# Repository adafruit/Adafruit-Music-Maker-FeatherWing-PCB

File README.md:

## Adafruit Music Maker FeatherWing PCB

<a href="http://www.adafruit.com/products/3357">&nbsp; 
<a href="http://www.adafruit.com/products/3436"><br/>
Click a picture to purchase from the Adafruit shop</a>

PCB files for the Adafruit Music Maker FeatherWings. Format is EagleCAD schematic and board layout

For more details, check out the product pages at
  * Music Maker FeatherWing http://www.adafruit.com/products/3357
  * Music Maker FeatherWing with 3W amp http://www.adafruit.com/products/3436

### Description

Bend all audio files to your will with the Adafruit Music Maker FeatherWings! It's a fun-size version of our Music Maker shield for Arduino! This powerful wing features the VS1053, an encoding/decoding (codec) chip that can decode a wide variety of audio formats such as MP3, AAC, Ogg Vorbis, WMA, MIDI, FLAC, WAV (PCM and ADPCM). You can do all sorts of stuff with the audio as well such as adjusting bass, treble, and volume digitally.

All this functionality is implemented in a light-weight SPI interface so that any Feather Board can play audio from an SD card. There's also a special MIDI mode that you can boot the chip into that will read 'classic' 31250Kbaud MIDI data from the UART TX pin and act like a synth/drum machine - there are dozens of built-in drum and sample effects!

What a great musical add-on to your Feather! That's why we spun up this super FeatherWing, perfect for use with any of our Feather Boards! Music playback testing working with ATmega32u4, ATSAMD M0, ESP8266, WICED Teensy 3, and nRF52 Feathers. MIDI playback works with all Feathers but you may need to remove the 'Wing during programming and also for USB-Serial Feathers like the ESP8266 and nRF52 you'll end up re-using the main Serial console for MIDI which can be confusing.

### License

Adafruit invests time and resources providing this open source design, please support Adafruit and open-source hardware by purchasing products from [Adafruit](https://www.adafruit.com)!

Designed by Limor Fried/Ladyada for Adafruit Industries.

Creative Commons Attribution/Share-Alike, all text above must be included in any redistribution. See license.txt for additional details.

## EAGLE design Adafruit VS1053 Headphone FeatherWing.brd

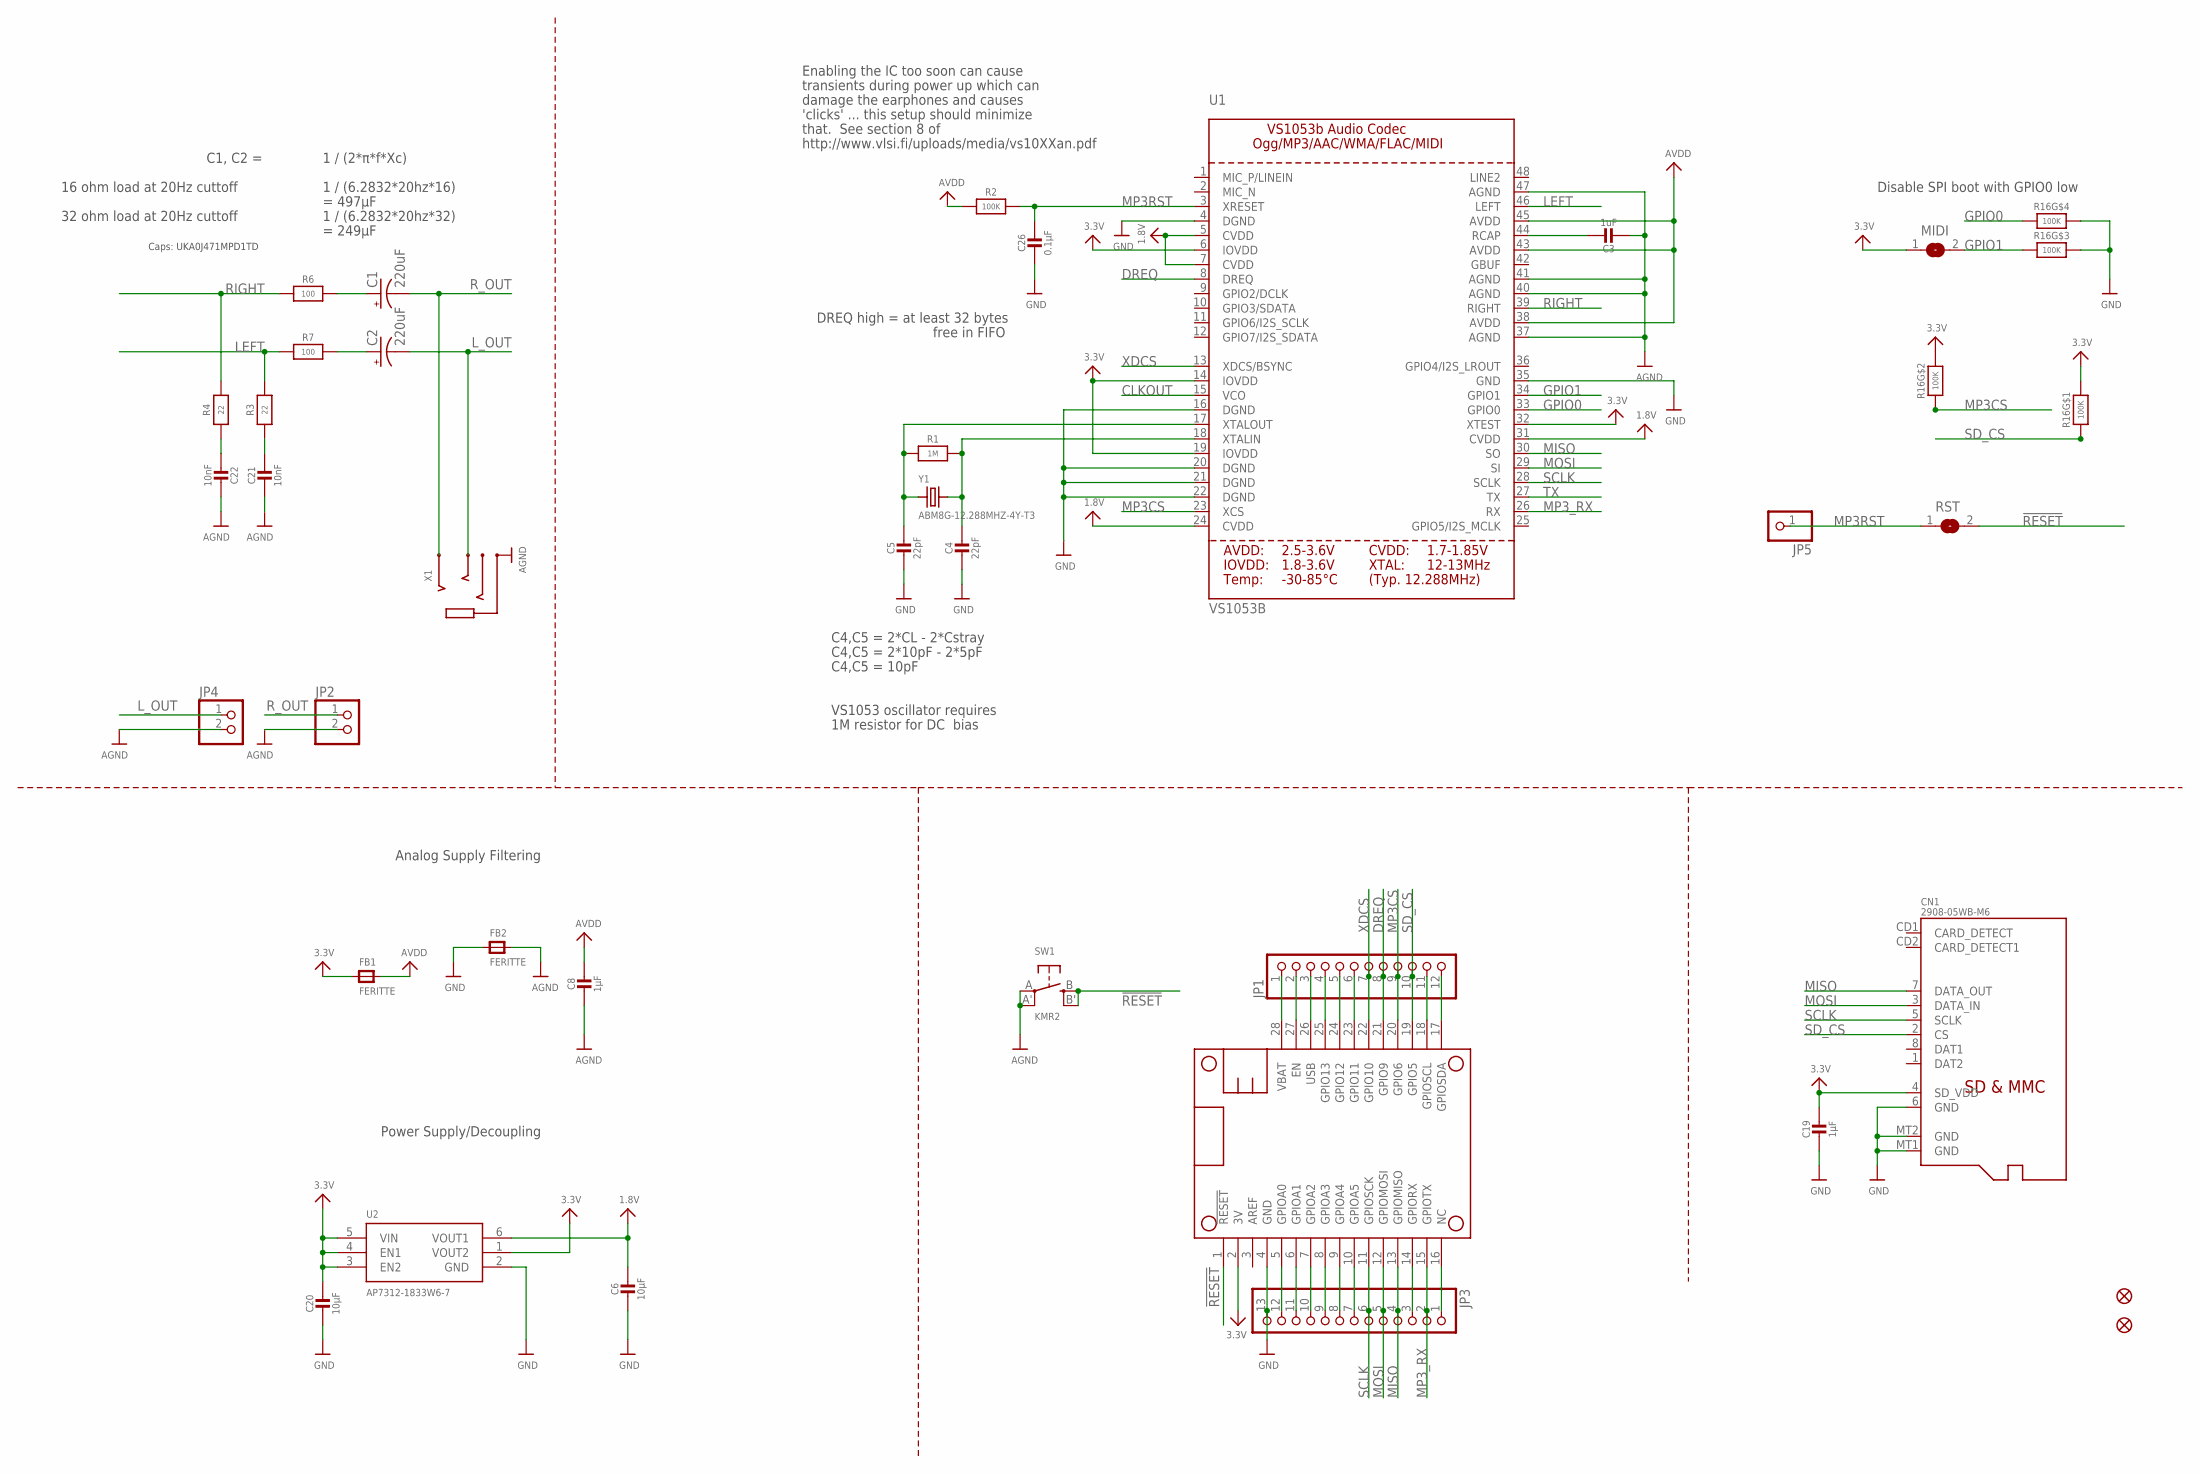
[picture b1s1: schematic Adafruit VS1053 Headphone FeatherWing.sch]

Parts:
C1, C2: 220uF; PANASONIC_C
C3: 1uF; 0603-NO
C4, C5: 22pF; 0603-NO
C6: 10µF; _0805MP
C8, C19: 1µF; 0603-NO
C20: 10µF; 0805-NO
C21, C22: 10nF; 0603-NO
C26: 0.1µF; 0603-NO
CN1: 2908-05WB-M6; MICROSD
FB1, FB2: FERITTE; 0805-NO
FID1, FID2: FIDUCIAL""; FIDUCIAL_1MM
JP1: HEADER-1X12; 1X12_ROUND
JP2, JP4: HEADER-1X2ROUND; 1X02_ROUND
JP3: HEADER-1X13; 1X13_ROUND_70
JP5: HEADER-1X1ROUND; 1X01_ROUND
MIDI: SOLDERJUMPER; SOLDERJUMPER_ARROW_NOPASTE
MS1: FEATHERWING_NODIM
R1: 1M; 0603-NO
R2: 100K; 0603-NO
R3, R4: 22; 0603-NO
R6, R7: 100; 0603-NO
R16: 100K; RESPACK_4X0603
RST: SOLDERJUMPERCLOSED; SOLDERJUMPER_CLOSEDWIRE
SW1: KMR2; BTN_KMR2_4.6X2.8
U1: VS1053B; LQFP48
U2: AP7312-1833W6-7; SOT23-6
X1: AUDIO_3.5MMJACK_4POL; 4UCONN_18510
Y1: ABM8G-12.288MHZ-4Y-T3; CRYSTAL_3.2X2.5

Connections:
1.8V: C6.1, U1.5 (CVDD), U1.7 (CVDD), U1.24 (CVDD), U1.31 (CVDD), U2.6 (VOUT1)
3.3V: C19.1, C20.1, CN1.4 (SD_VDD), FB1.1, MIDI.1, MS1.2 (3V), R16.7 (2), R16.8 (2), U1.6 (IOVDD), U1.14 (IOVDD), U1.19 (IOVDD), U1.32 (XTEST), U2.1 (VOUT2), U2.3 (EN2), U2.4 (EN1), U2.5 (VIN)
!RESET: MS1.1 (!RESET), RST.2, SW1.B (S), SW1.B' (S1)
AGND: C3.2, C8.2, C21.2, C22.2, FB2.2, JP2.2, JP4.2, SW1.A, SW1.A' (P1), U1.37 (AGND), U1.40 (AGND), U1.41 (AGND), U1.47 (AGND), X1.1-GND (TIP)
AVDD: C8.1, FB1.2, R2.1, U1.38 (AVDD), U1.43 (AVDD), U1.45 (AVDD)
CLKOUT: U1.15 (VCO)
DREQ: JP1.8, MS1.21 (GPIO9), U1.8 (DREQ)
GND: C4.2, C5.2, C6.2, C19.2, C20.2, C26.2, CN1.6 (GND), CN1.MT1 (GND), CN1.MT2 (GND), FB2.1, JP3.13, MS1.4 (GND), R16.5 (2), R16.6 (2), U1.4 (DGND), U1.16 (DGND), U1.20 (DGND), U1.21 (DGND), U1.22 (DGND), U1.35 (GND), U2.2 (GND)
GPIO0: R16.4 (1), U1.33 (GPIO0)
GPIO1: MIDI.2, R16.3 (1), U1.34 (GPIO1)
LEFT: R3.1, R7.2, U1.46 (LEFT)
LEFT_FILTERED: C2.+, R7.1
L_OUT: C2.-, JP4.1, X1.2-TIP (RING3)
MISO: CN1.7 (DATA_OUT), JP3.4, MS1.13 (GPIOMISO), U1.30 (SO)
MOSI: CN1.3 (DATA_IN), JP3.5, MS1.12 (GPIOMOSI), U1.29 (SI)
MP3CS: JP1.9, MS1.20 (GPIO6), R16.2 (1), U1.23 (XCS)
MP3RST: C26.1, JP5.1, R2.2, RST.1, U1.3 (XRESET)
MP3_RX: JP3.2, MS1.15 (GPIOTX), U1.26 (RX)
unnamed: C5.1, R1.1, U1.17 (XTALOUT), Y1.1
unnamed: C4.1, R1.2, U1.18 (XTALIN), Y1.2
unnamed: C3.1, U1.44 (RCAP)
unnamed: JP1.2, MS1.27 (EN)
unnamed: C21.1, R3.2
unnamed: C22.1, R4.2
unnamed: JP1.4, MS1.25 (GPIO13)
unnamed: JP1.5, MS1.24 (GPIO12)
unnamed: JP1.6, MS1.23 (GPIO11)
unnamed: JP1.11, MS1.18 (GPIOSCL)
unnamed: JP1.12, MS1.17 (GPIOSDA)
unnamed: JP3.1, MS1.16 (NC)
unnamed: JP3.3, MS1.14 (GPIORX)
unnamed: JP3.7, MS1.10 (GPIOA5)
unnamed: JP3.8, MS1.9 (GPIOA4)
unnamed: JP3.9, MS1.8 (GPIOA3)
unnamed: JP3.10, MS1.7 (GPIOA2)
unnamed: JP3.11, MS1.6 (GPIOA1)
unnamed: JP3.12, MS1.5 (GPIOA0)
RIGHT: R4.1, R6.2, U1.39 (RIGHT)
RIGHT_FILTERED: C1.+, R6.1
R_OUT: C1.-, JP2.1, X1.3-OUTER_SLEEVE (RING2)
SCLK: CN1.5 (SCLK), JP3.6, MS1.11 (GPIOSCK), U1.28 (SCLK)
SD_CS: CN1.2 (CS), JP1.10, MS1.19 (GPIO5), R16.1
TX: U1.27 (TX)
USB: JP1.3, MS1.26 (USB)
VBAT: JP1.1, MS1.28 (VBAT)
XDCS: JP1.7, MS1.22 (GPIO10), U1.13 (XDCS/BSYNC)

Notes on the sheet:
Analog Supply Filtering
C4,C5 = 2*CL - 2*Cstray
C4,C5 = 2*10pF - 2*5pF
C4,C5 = 10pF
VS1053 oscillator requires
1M resistor for DC bias
DREQ high = at least 32 bytes
Power Supply/Decoupling
transients during power up which can
damage the earphones and causes
'clicks' ... this setup should minimize
that. See section 8 of
http://www.vlsi.fi/uploads/media/vs10XXan.pdf
Enabling the IC too soon can cause
free in FIFO
Disable SPI boot with GPIO0 low
1 / (2*π*f*Xc)
16 ohm load at 20Hz cuttoff
1 / (6.2832*20hz*16)
C1, C2 =
= 497µF
32 ohm load at 20Hz cuttoff
1 / (6.2832*20hz*32)
= 249µF
Caps: UKA0J471MPD1TD

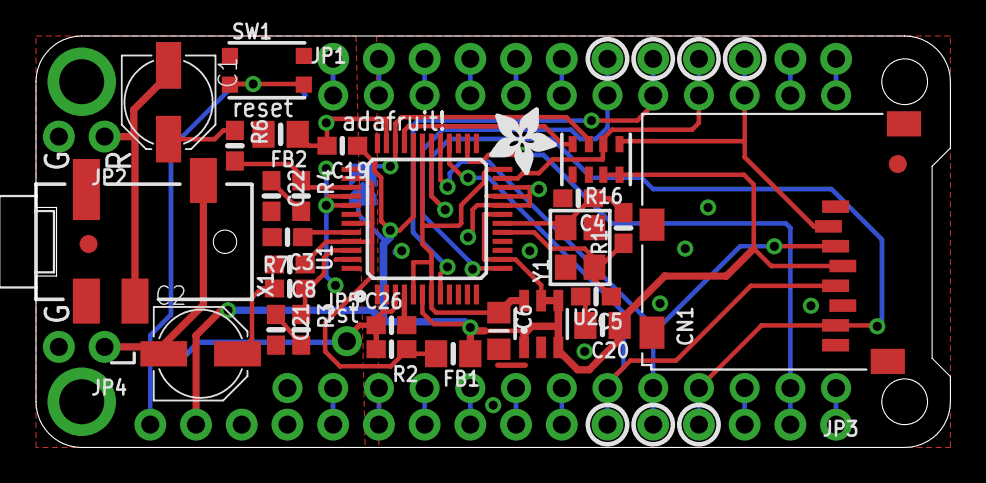
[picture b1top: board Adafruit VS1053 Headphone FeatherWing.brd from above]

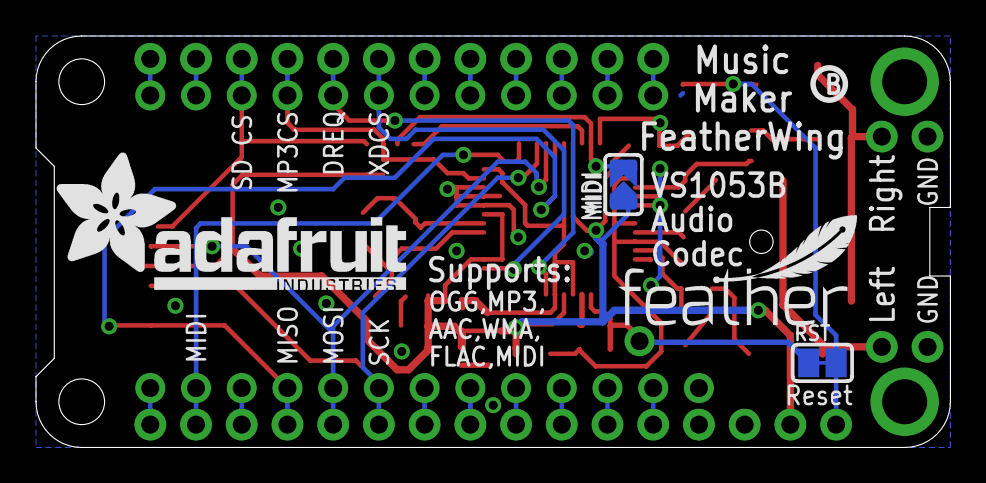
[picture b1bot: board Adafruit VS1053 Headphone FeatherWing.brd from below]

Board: 2 copper layers, 50.8 x 22.9 mm, 41 parts (5 on the bottom side), 44 nets.

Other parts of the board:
U$36: ADAFRUIT_3.5MM
U$37: FEATHERLOGO_SMALL
U$43: PCBFEAT-REV-040
U$55: ADAFRUIT_TEXT_20MM

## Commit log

2016-12-14 init
2017-03-22 add new amp version!
